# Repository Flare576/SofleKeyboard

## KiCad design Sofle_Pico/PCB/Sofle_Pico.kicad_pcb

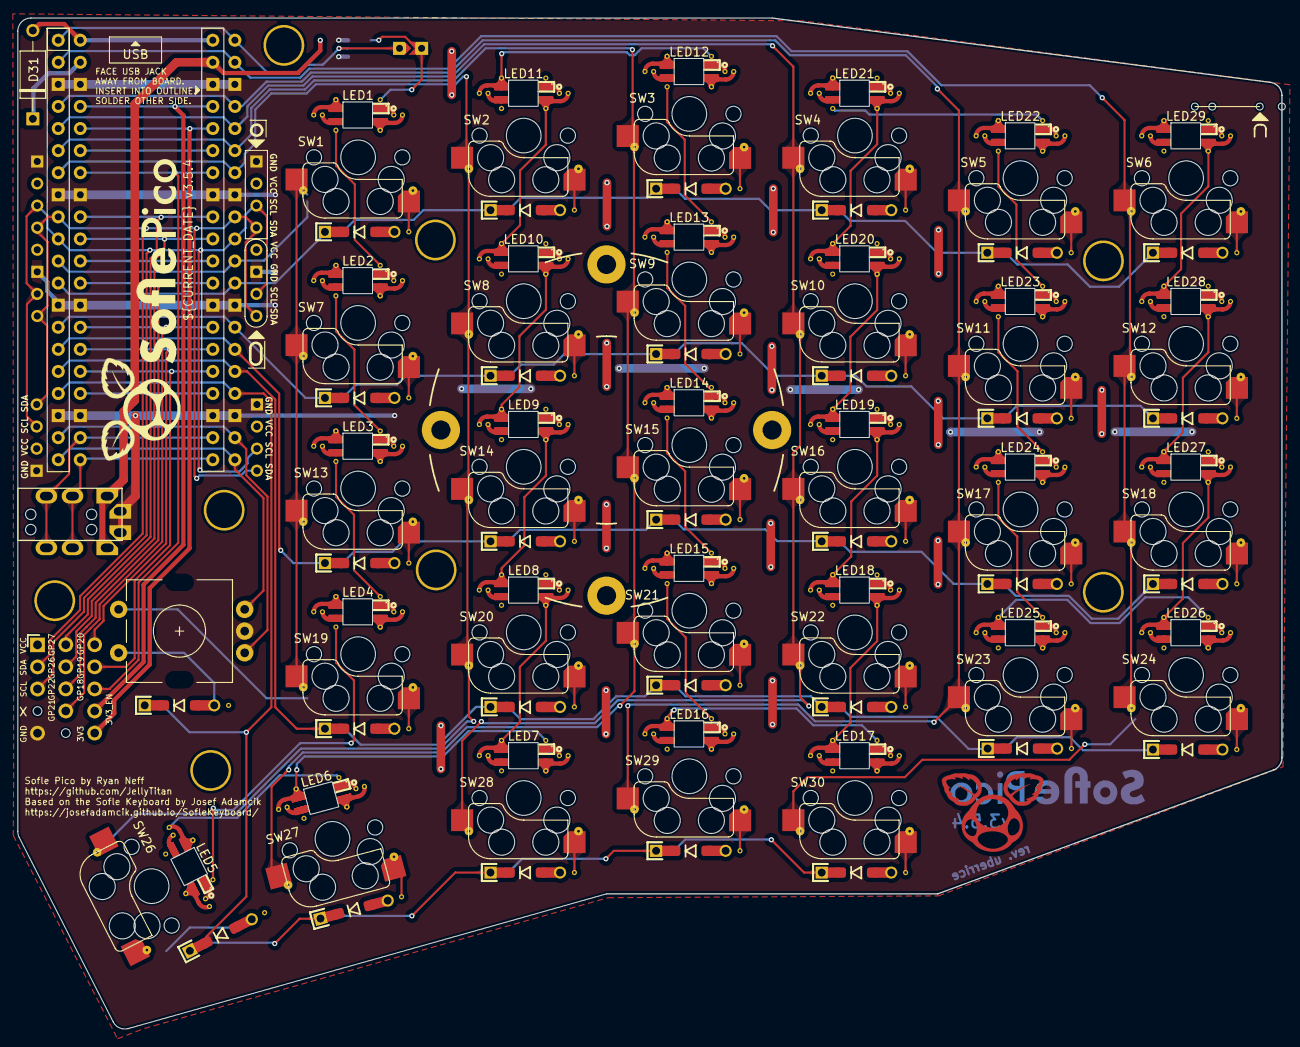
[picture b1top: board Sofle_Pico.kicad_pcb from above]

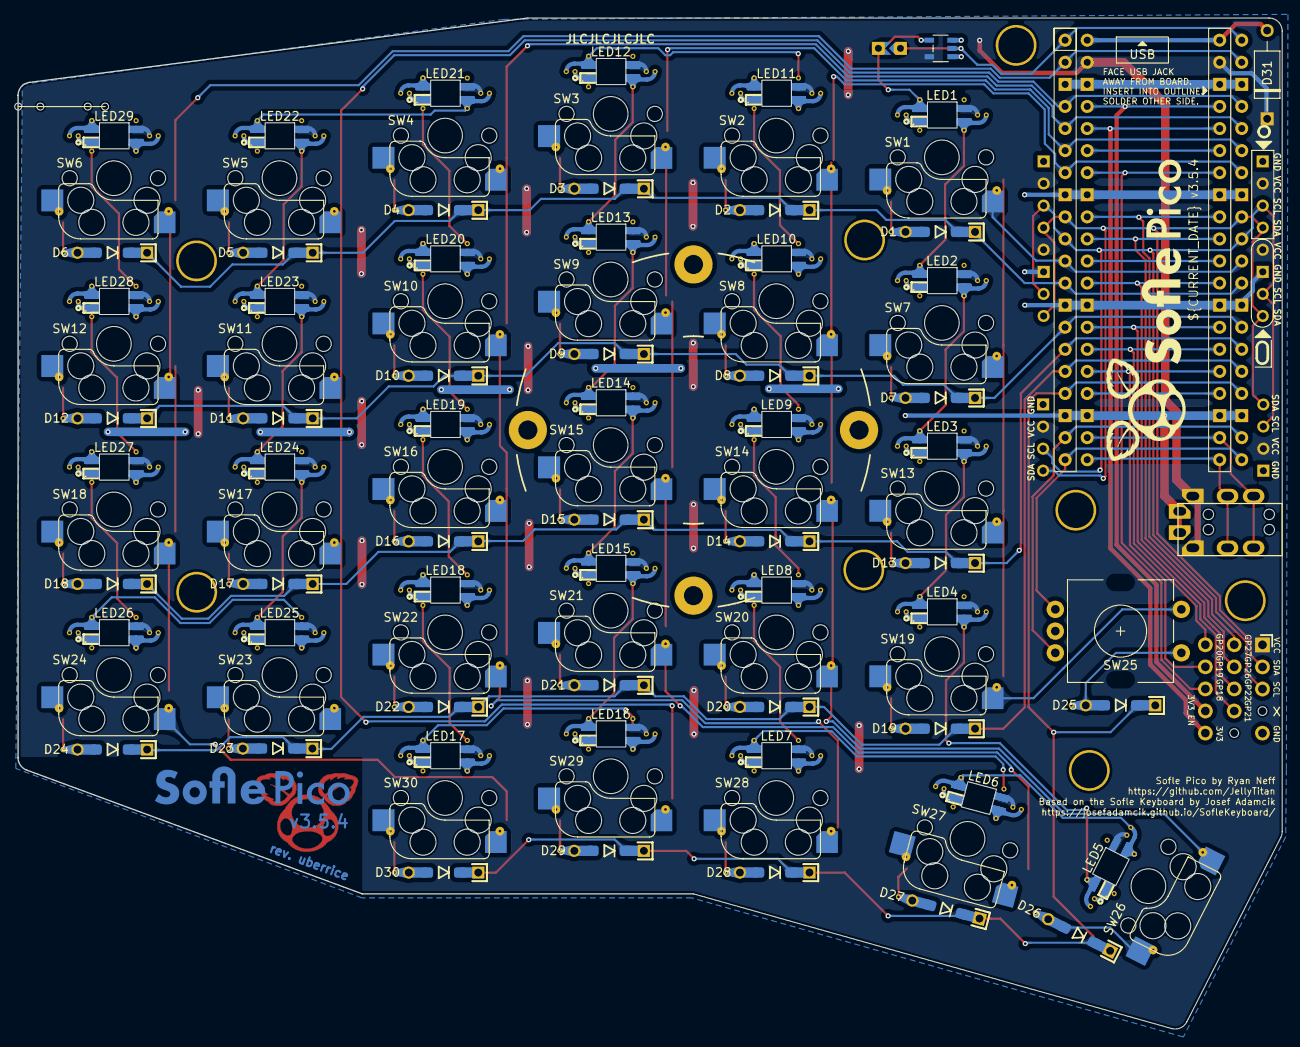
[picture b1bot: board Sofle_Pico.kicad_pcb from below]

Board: 2 copper layers, 145.4 x 116.3 mm, 108 parts (89 on the bottom side), 89 nets.

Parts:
D1, D2, D3, D4, D5, D6, D7, D8, D9, D10, D11, D12, D13, D14, D15, D16, D17, D18, D19, D20, D21, D22, D23, D24, D25, D26, D27, D28, D29, D30: D; D_SOD-123_DO-35_Hybrid_DoubleSided_V2
D31: 1N5817; D_DO-41_SOD81_P10.16mm_Horizontal
J1: Conn_01x05; Pimaroni_PinHeader_1x05_P2.54mm_Vertical Sofle v3b
J2: MJ-4PP-9
J3: Conn_01x04; OLED SSD1306 128x64
J4, J7: Conn_01x04; Cirque tie in
J5: Conn_01x05; PinHeader_1x05_P2.54mm_Vertical_one-dead
J6: Conn_01x05; PinHeader_1x05_P2.54mm_Vertical
JP1: Level shifter bypass jumper; Level Shifter Bypass Jumper
LED1, LED2, LED3, LED4, LED5, LED6, LED7, LED8, LED9, LED10, LED11, LED12, LED13, LED14, LED15, LED16, LED17, LED18, LED19, LED20, LED21, LED22, LED23, LED24, LED25, LED26, LED27, LED28, LED29: SK6803 MINI-E; SK6803_MINIE_v3.5.4
SW1, SW2, SW3, SW4, SW5, SW6, SW7, SW8, SW9, SW10, SW11, SW12, SW13, SW14, SW15, SW16, SW17, SW18, SW19, SW20, SW21, SW22, SW23, SW24, SW26, SW27, SW28, SW29, SW30: SW_PUSH_LED; Cherry_MX_DS_Hotswap_v3.5.4
SW25: Rotary_Encoder_Switch-Device; RotaryEncoder_Alps_EC11E-Switch_Vertical_H20mm-keebio_modif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
TH1, TH2, TH7: HOLE; Hole from sofle for M2 posts gold rimmer wide-keyplate-hole
TH3, TH4, TH5, TH6, TH8: HOLE; Hole from sofle for M2 posts gold rimmer
U1: SN74AHCT1G125
U2: Pico; RPi_Pico_SMD_TH_DS

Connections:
3V3: J6.5, U2.36 (3V3)
3V3_EN: J6.4, U2.37 (3V3_EN)
ENCA: SW25.A, U2.19 (GPIO14)
ENCB: SW25.B, U2.20 (GPIO15)
GND: J1.5, J2.1, J3.4, J4.4, J7.4, LED1.3 (GND), LED2.3 (GND), LED3.3 (GND), LED4.3 (GND), LED5.3 (GND), LED6.3 (GND), LED7.3 (GND), LED8.3 (GND), LED9.3 (GND), LED10.3 (GND), LED11.3 (GND), LED12.3 (GND), LED13.3 (GND), LED14.3 (GND), LED15.3 (GND), LED16.3 (GND), LED17.3 (GND), LED18.3 (GND), LED19.3 (GND), LED20.3 (GND), LED21.3 (GND), LED22.3 (GND), LED23.3 (GND), LED24.3 (GND), LED25.3 (GND), LED26.3 (GND), LED27.3 (GND), LED28.3 (GND), LED29.3 (GND), SW25.C, U1.1 (OE), U1.3 (GND), U2.3 (GND), U2.8 (GND), U2.13 (GND), U2.18 (GND), U2.23 (GND), U2.28 (GND), U2.33 (AGND), U2.38 (GND)
GP19: J6.2, U2.25 (GPIO19)
GP20: J6.1, U2.26 (GPIO20)
GP21: J5.4, U2.27 (GPIO21)
GP22: J5.3, U2.29 (GPIO22)
GP26: J5.2, U2.31 (GPIO26_ADC0)
GP27: J5.1, U2.32 (GPIO27_ADC1)
GP28: J6.3, U2.34 (GPIO28_ADC2)
LED: JP1.1 (A), U1.2 (DIN), U2.1 (GPIO0)
unnamed: D1.2 (A), SW1.2
unnamed: D2.2 (A), SW2.2
unnamed: D3.2 (A), SW3.2
unnamed: D4.2 (A), SW4.2
unnamed: D5.2 (A), SW5.2
unnamed: D6.2 (A), SW6.2
unnamed: D7.2 (A), SW7.2
unnamed: D8.2 (A), SW8.2
unnamed: D9.2 (A), SW9.2
unnamed: D10.2 (A), SW10.2
unnamed: D11.2 (A), SW11.2
unnamed: D12.2 (A), SW12.2
unnamed: D13.2 (A), SW13.2
unnamed: D14.2 (A), SW14.2
unnamed: D15.2 (A), SW15.2
unnamed: D16.2 (A), SW16.2
unnamed: D17.2 (A), SW17.2
unnamed: D18.2 (A), SW18.2
unnamed: D19.2 (A), SW19.2
unnamed: D20.2 (A), SW20.2
unnamed: D21.2 (A), SW21.2
unnamed: D22.2 (A), SW22.2
unnamed: D23.2 (A), SW23.2
unnamed: D24.2 (A), SW24.2
unnamed: D26.2 (A), SW26.2
unnamed: D27.2 (A), SW27.2
unnamed: D28.2 (A), SW28.2
unnamed: D29.2 (A), SW29.2
unnamed: D30.2 (A), SW30.2
unnamed: D31.2 (A), U2.40 (VBUS)
unnamed: JP1.2 (B), LED1.4 (DIN), U1.4 (DOUT)
unnamed: LED1.2 (DOUT), LED2.4 (DIN)
unnamed: LED2.2 (DOUT), LED3.4 (DIN)
unnamed: LED3.2 (DOUT), LED4.4 (DIN)
unnamed: LED4.2 (DOUT), LED5.4 (DIN)
unnamed: LED5.2 (DOUT), LED6.4 (DIN)
unnamed: LED6.2 (DOUT), LED7.4 (DIN)
unnamed: LED7.2 (DOUT), LED8.4 (DIN)
unnamed: LED8.2 (DOUT), LED9.4 (DIN)
unnamed: LED9.2 (DOUT), LED10.4 (DIN)
unnamed: LED10.2 (DOUT), LED11.4 (DIN)
unnamed: LED11.2 (DOUT), LED12.4 (DIN)
unnamed: LED12.2 (DOUT), LED13.4 (DIN)
unnamed: LED13.2 (DOUT), LED14.4 (DIN)
unnamed: LED14.2 (DOUT), LED15.4 (DIN)
unnamed: LED15.2 (DOUT), LED16.4 (DIN)
unnamed: LED16.2 (DOUT), LED17.4 (DIN)
unnamed: LED17.2 (DOUT), LED18.4 (DIN)
unnamed: LED18.2 (DOUT), LED19.4 (DIN)
unnamed: LED19.2 (DOUT), LED20.4 (DIN)
unnamed: LED20.2 (DOUT), LED21.4 (DIN)
unnamed: LED21.2 (DOUT), LED22.4 (DIN)
unnamed: LED22.2 (DOUT), LED23.4 (DIN)
unnamed: LED23.2 (DOUT), LED24.4 (DIN)
unnamed: LED24.2 (DOUT), LED25.4 (DIN)
unnamed: LED25.2 (DOUT), LED26.4 (DIN)
unnamed: LED26.2 (DOUT), LED27.4 (DIN)
unnamed: LED27.2 (DOUT), LED28.4 (DIN)
unnamed: LED28.2 (DOUT), LED29.4 (DIN)
RX: J2.4, U2.22 (GPIO17)
SCL: J1.3, J3.2, J4.2, J7.2, U2.10 (GPIO7)
SDA: J1.2, J3.1, J4.1, J7.1, U2.9 (GPIO6)
SW25A: SW1.1, SW7.1, SW13.1, SW19.1, SW25.S1, U2.11 (GPIO8)
SW25B: D25.2 (A), SW25.S2
TX: J2.3, U2.21 (GPIO16)
VCC: D31.1 (K), J1.1, J2.2, J3.3, J4.3, J7.3, LED1.1 (VDD), LED2.1 (VDD), LED3.1 (VDD), LED4.1 (VDD), LED5.1 (VDD), LED6.1 (VDD), LED7.1 (VDD), LED8.1 (VDD), LED9.1 (VDD), LED10.1 (VDD), LED11.1 (VDD), LED12.1 (VDD), LED13.1 (VDD), LED14.1 (VDD), LED15.1 (VDD), LED16.1 (VDD), LED17.1 (VDD), LED18.1 (VDD), LED19.1 (VDD), LED20.1 (VDD), LED21.1 (VDD), LED22.1 (VDD), LED23.1 (VDD), LED24.1 (VDD), LED25.1 (VDD), LED26.1 (VDD), LED27.1 (VDD), LED28.1 (VDD), LED29.1 (VDD), U1.5 (VCC), U2.39 (VSYS)
col0: SW6.1, SW12.1, SW18.1, SW24.1, SW30.1, U2.2 (GPIO1)
col1: SW5.1, SW11.1, SW17.1, SW23.1, SW29.1, U2.4 (GPIO2)
col2: SW4.1, SW10.1, SW16.1, SW22.1, SW28.1, U2.5 (GPIO3)
col3: SW3.1, SW9.1, SW15.1, SW21.1, SW27.1, U2.6 (GPIO4)
col4: SW2.1, SW8.1, SW14.1, SW20.1, SW26.1, U2.7 (GPIO5)
row0: D1.1 (K), D2.1 (K), D3.1 (K), D4.1 (K), D5.1 (K), D6.1 (K), U2.12 (GPIO9)
row1: D7.1 (K), D8.1 (K), D9.1 (K), D10.1 (K), D11.1 (K), D12.1 (K), U2.14 (GPIO10)
row2: D13.1 (K), D14.1 (K), D15.1 (K), D16.1 (K), D17.1 (K), D18.1 (K), U2.15 (GPIO11)
row3: D19.1 (K), D20.1 (K), D21.1 (K), D22.1 (K), D23.1 (K), D24.1 (K), U2.16 (GPIO12)
row4: D25.1 (K), D26.1 (K), D27.1 (K), D28.1 (K), D29.1 (K), D30.1 (K), U2.17 (GPIO13)

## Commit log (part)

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2026-06-28 docs(buildguide): add wireless build guide
    Adds full build guide with images following the current standard format
2026-06-28 fix(images): remove unused images
2026-06-29 fix(typos): had my clanker review human slop
